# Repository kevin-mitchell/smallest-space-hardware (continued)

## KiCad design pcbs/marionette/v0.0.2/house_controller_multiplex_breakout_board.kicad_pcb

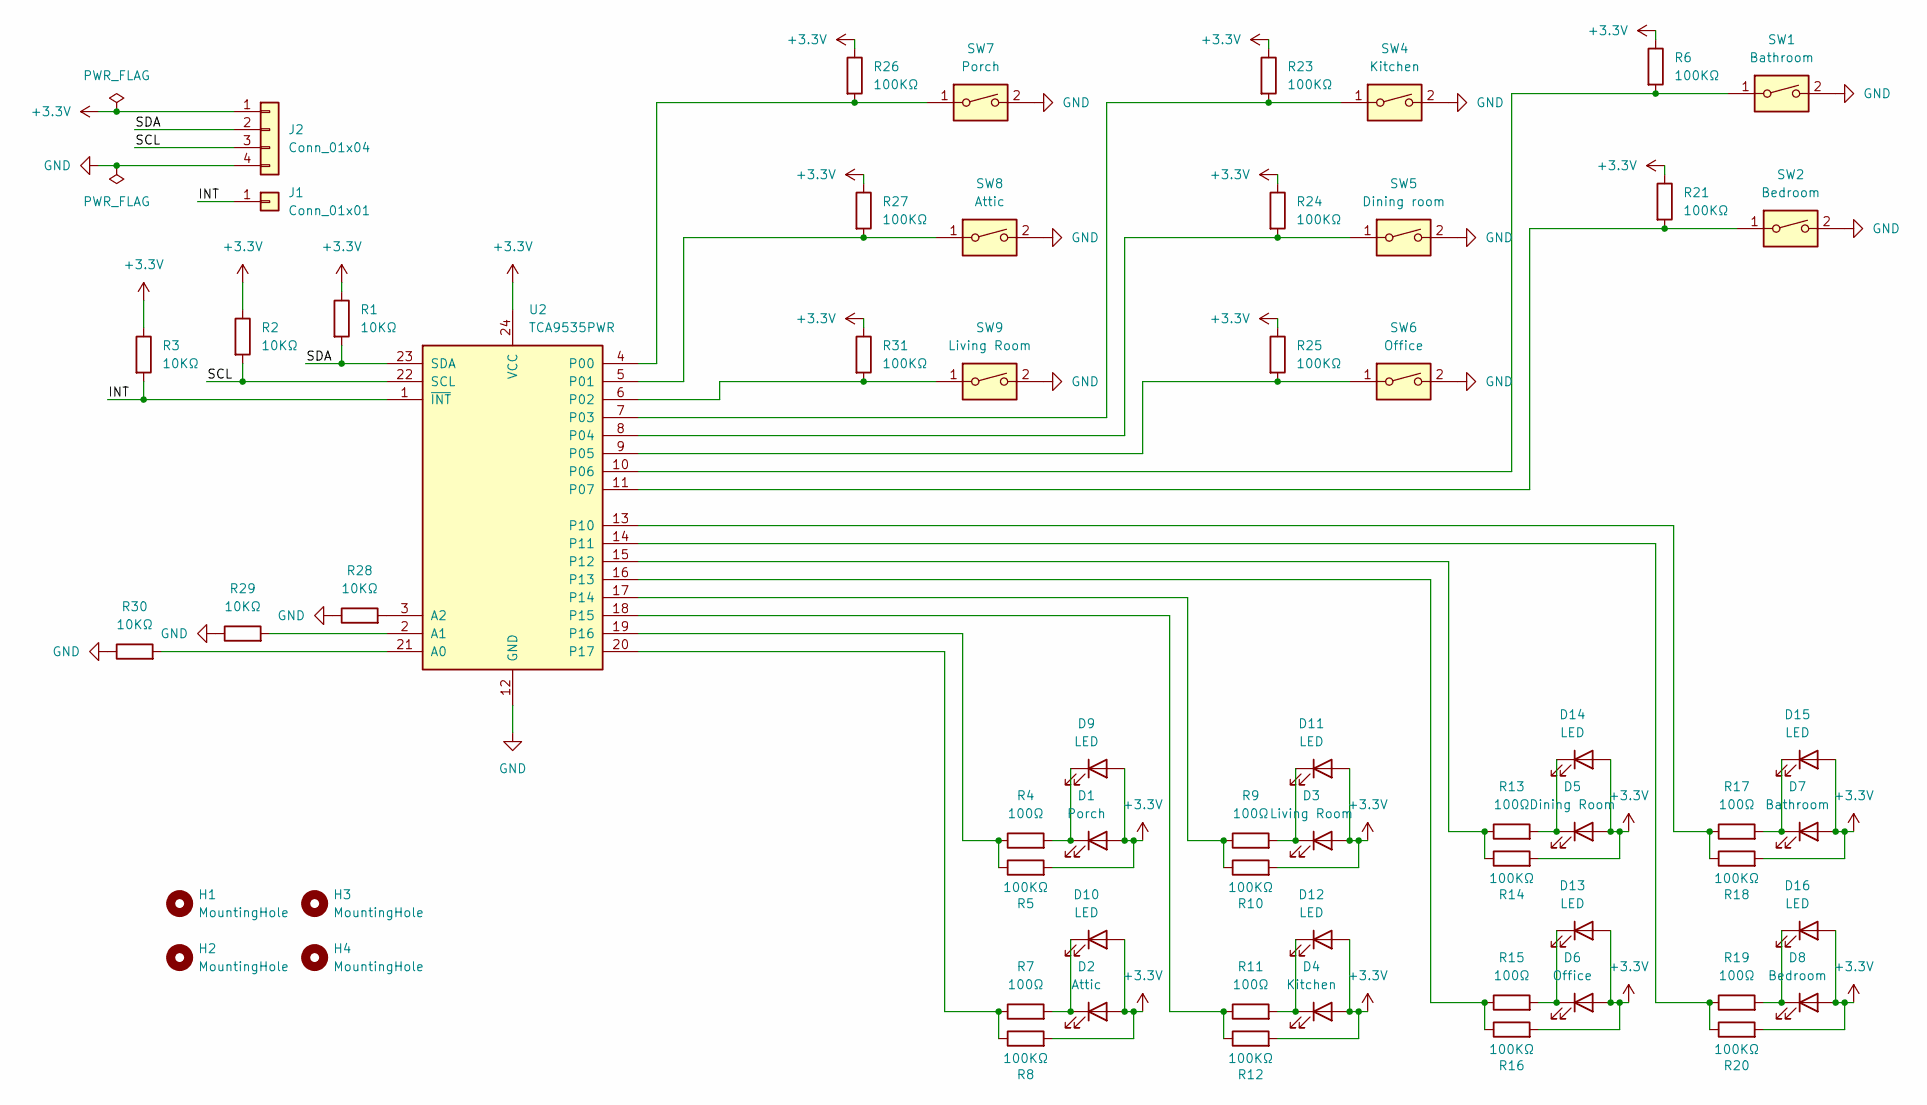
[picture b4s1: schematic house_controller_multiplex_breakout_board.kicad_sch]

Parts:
D1: Porch; LED_0805_2012Metric_Pad1.15x1.40mm_HandSolder
D2: Attic; LED_0805_2012Metric_Pad1.15x1.40mm_HandSolder
D3: Living Room; LED_0805_2012Metric_Pad1.15x1.40mm_HandSolder
D4: Kitchen; LED_0805_2012Metric_Pad1.15x1.40mm_HandSolder
D5: Dining Room; LED_0805_2012Metric_Pad1.15x1.40mm_HandSolder
D6: Office; LED_0805_2012Metric_Pad1.15x1.40mm_HandSolder
D7: Bathroom; LED_0805_2012Metric_Pad1.15x1.40mm_HandSolder
D8: Bedroom; LED_0805_2012Metric_Pad1.15x1.40mm_HandSolder
D9, D10, D11, D12, D13, D14, D15, D16: LED; LED_D3.0mm
H1, H2, H3, H4: MountingHole; MountingHole_2.5mm
J1: Conn_01x01; PinSocket_1x01_P2.54mm_Vertical
J2: Conn_01x04; PinSocket_1x04_P2.54mm_Vertical
R1, R2, R3, R28, R29, R30: 10KΩ; R_0805_2012Metric_Pad1.20x1.40mm_HandSolder
R4, R7, R9, R11, R13, R15, R17, R19: 100Ω; R_0805_2012Metric_Pad1.20x1.40mm_HandSolder
R5, R6, R8, R10, R12, R14, R16, R18, R20, R21, R23, R24, R25, R26, R27, R31: 100KΩ; R_0805_2012Metric_Pad1.20x1.40mm_HandSolder
SW1: Bathroom; SW_DIP_SPSTx01_Slide_9.78x4.72mm_W7.62mm_P2.54mm
SW2: Bedroom; SW_DIP_SPSTx01_Slide_9.78x4.72mm_W7.62mm_P2.54mm
SW4: Kitchen; SW_DIP_SPSTx01_Slide_9.78x4.72mm_W7.62mm_P2.54mm
SW5: Dining room; SW_DIP_SPSTx01_Slide_9.78x4.72mm_W7.62mm_P2.54mm
SW6: Office; SW_DIP_SPSTx01_Slide_9.78x4.72mm_W7.62mm_P2.54mm
SW7: Porch; SW_DIP_SPSTx01_Slide_9.78x4.72mm_W7.62mm_P2.54mm
SW8: Attic; SW_DIP_SPSTx01_Slide_9.78x4.72mm_W7.62mm_P2.54mm
SW9: Living Room; SW_DIP_SPSTx01_Slide_9.78x4.72mm_W7.62mm_P2.54mm
U2: TCA9535PWR; TSSOP-24_4.4x7.8mm_P0.65mm

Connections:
+3.3V: D1.2 (A), D2.2 (A), D3.2 (A), D4.2 (A), D5.2 (A), D6.2 (A), D7.2 (A), D8.2 (A), D9.2 (A), D10.2 (A), D11.2 (A), D12.2 (A), D13.2 (A), D14.2 (A), D15.2 (A), D16.2 (A), J2.1, R1.1, R2.1, R3.1, R5.2, R6.1, R8.2, R10.2, R12.2, R14.2, R16.2, R18.2, R20.2, R21.1, R23.1, R24.1, R25.1, R26.1, R27.1, R31.1, U2.24 (VCC)
/INT: J1.1, R3.2, U2.1 (~INT)
/SCL: J2.3, R2.2, U2.22 (SCL)
/SDA: J2.2, R1.2, U2.23 (SDA)
GND: J2.4, R28.1, R29.1, R30.1, SW1.2, SW2.2, SW4.2, SW5.2, SW6.2, SW7.2, SW8.2, SW9.2, U2.12 (GND)
unnamed: D1.1 (K), D9.1 (K), R4.2
unnamed: D2.1 (K), D10.1 (K), R7.2
unnamed: D3.1 (K), D11.1 (K), R9.2
unnamed: D4.1 (K), D12.1 (K), R11.2
unnamed: D6.1 (K), D13.1 (K), R15.2
unnamed: D5.1 (K), D14.1 (K), R13.2
unnamed: D7.1 (K), D15.1 (K), R17.2
unnamed: D8.1 (K), D16.1 (K), R19.2
unnamed: R30.2, U2.21 (A0)
unnamed: R29.2, U2.2 (A1)
unnamed: R28.2, U2.3 (A2)
unnamed: R26.2, SW7.1, U2.4 (P00)
unnamed: R27.2, SW8.1, U2.5 (P01)
unnamed: R31.2, SW9.1, U2.6 (P02)
unnamed: R23.2, SW4.1, U2.7 (P03)
unnamed: R24.2, SW5.1, U2.8 (P04)
unnamed: R25.2, SW6.1, U2.9 (P05)
unnamed: R6.2, SW1.1, U2.10 (P06)
unnamed: R21.2, SW2.1, U2.11 (P07)
unnamed: R17.1, R18.1, U2.13 (P10)
unnamed: R19.1, R20.1, U2.14 (P11)
unnamed: R13.1, R14.1, U2.15 (P12)
unnamed: R15.1, R16.1, U2.16 (P13)
unnamed: R9.1, R10.1, U2.17 (P14)
unnamed: R11.1, R12.1, U2.18 (P15)
unnamed: R4.1, R5.1, U2.19 (P16)
unnamed: R7.1, R8.1, U2.20 (P17)

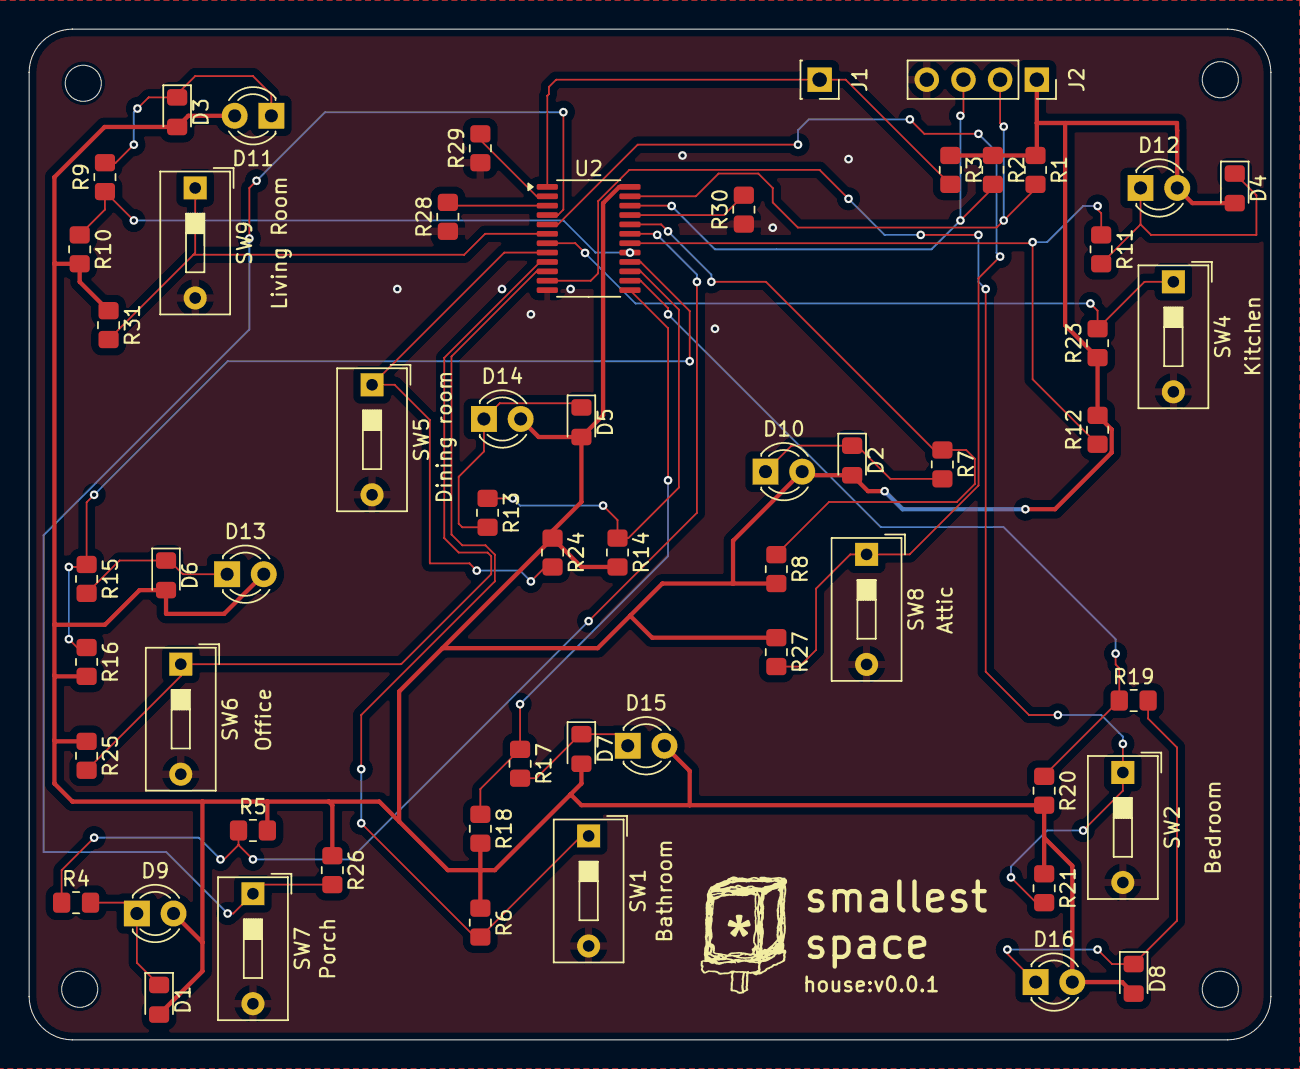
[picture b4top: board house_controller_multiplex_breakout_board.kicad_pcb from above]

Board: 4 copper layers, 86.0 x 70.0 mm, 61 parts (0 on the bottom side), 32 nets.

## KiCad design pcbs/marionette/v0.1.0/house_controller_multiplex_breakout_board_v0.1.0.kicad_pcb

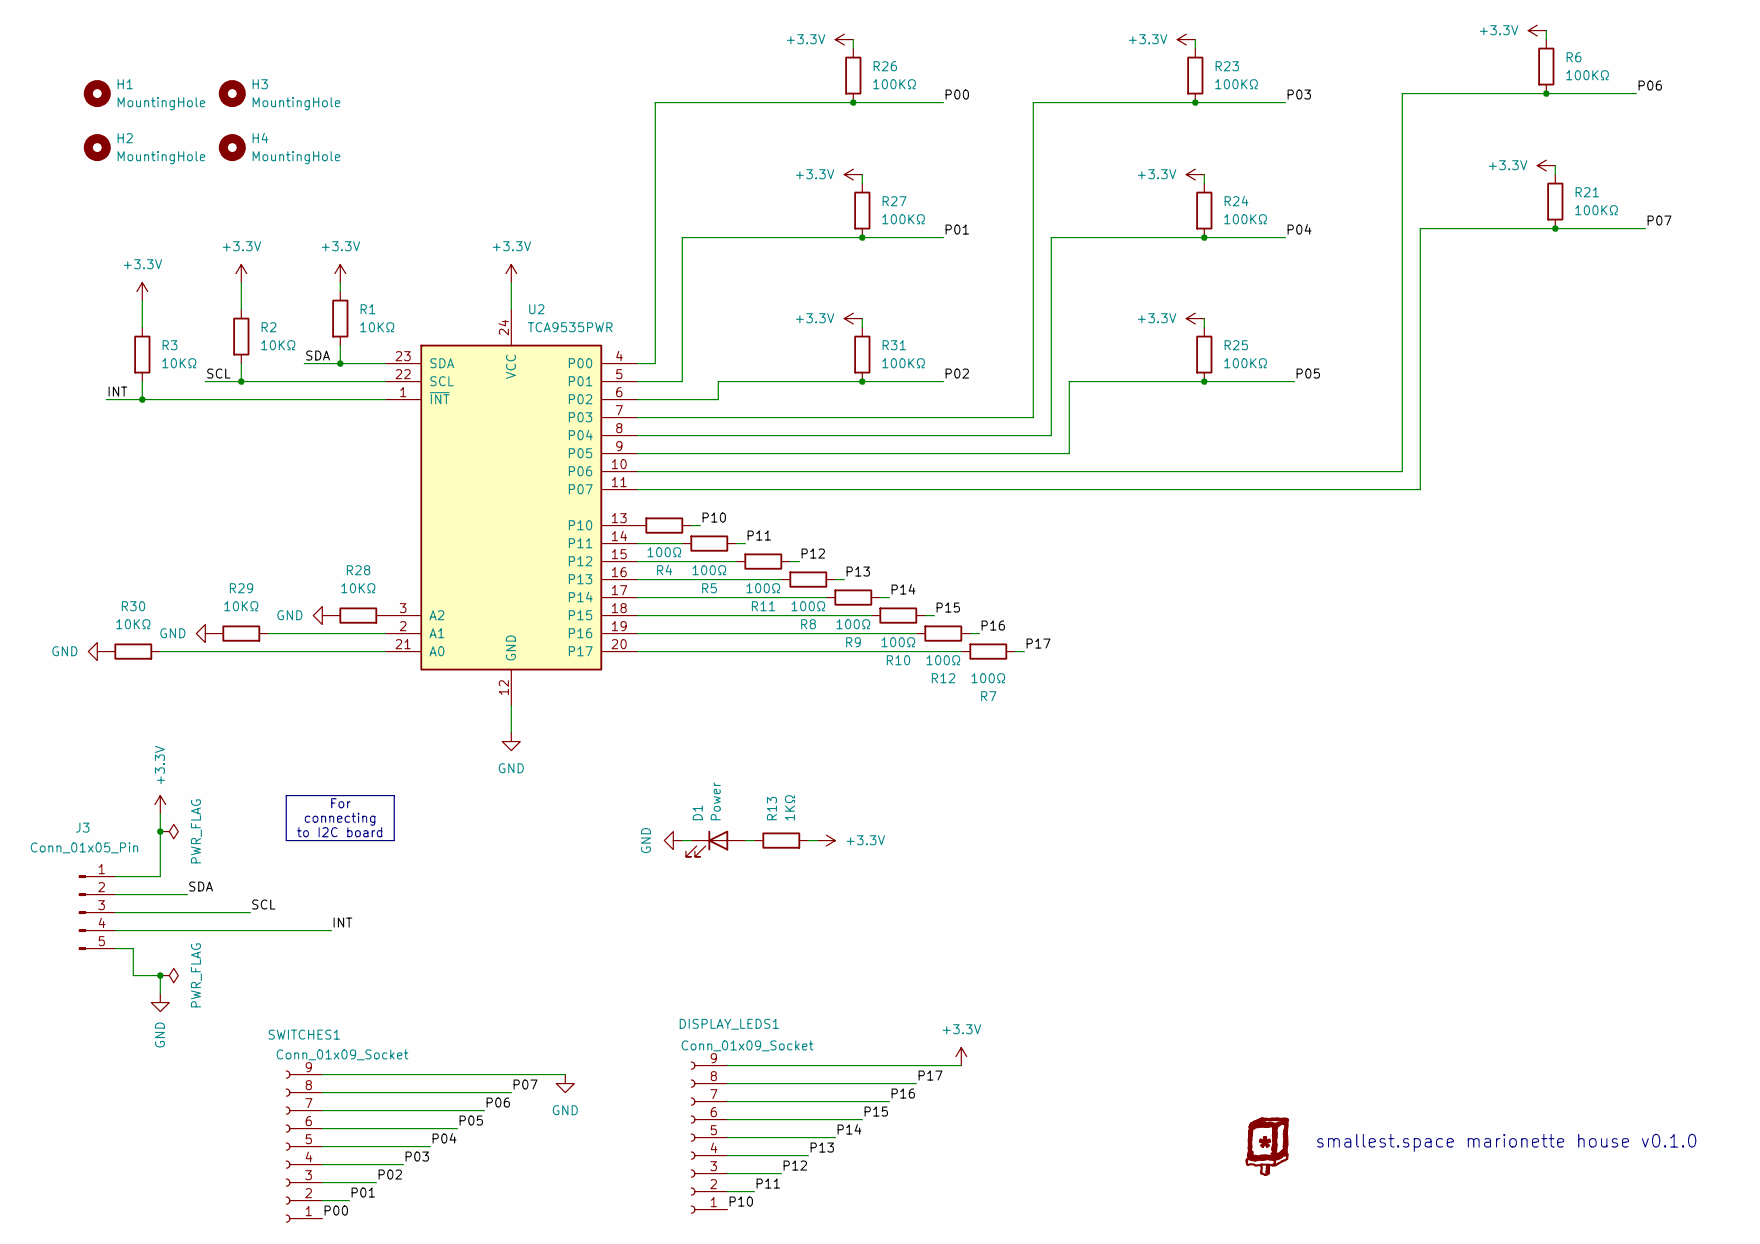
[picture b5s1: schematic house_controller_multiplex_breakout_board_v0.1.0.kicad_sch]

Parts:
D1: Power; LED_0805_2012Metric_Pad1.15x1.40mm_HandSolder
DISPLAY_LEDS1: Conn_01x09_Socket; TBL009-254-09XX-2XX
H1, H2, H3, H4: MountingHole; MountingHole_2.5mm
J3: Conn_01x05_Pin; JST_S05B-PASK-2_1x05_P2.00mm_Side_entry
R1, R2, R3, R28, R29, R30: 10KΩ; R_0805_2012Metric_Pad1.20x1.40mm_HandSolder
R4, R5, R7, R8, R9, R10, R11, R12: 100Ω; R_0805_2012Metric_Pad1.20x1.40mm_HandSolder
R6, R21, R23, R24, R25, R26, R27, R31: 100KΩ; R_0805_2012Metric_Pad1.20x1.40mm_HandSolder
R13: 1KΩ; R_0805_2012Metric_Pad1.20x1.40mm_HandSolder
SWITCHES1: Conn_01x09_Socket; TBL009-254-09XX-2XX
U2: TCA9535PWR; TSSOP-24_4.4x7.8mm_P0.65mm

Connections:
+3.3V: DISPLAY_LEDS1.9, J3.1, R1.1, R2.1, R3.1, R6.1, R13.2, R21.1, R23.1, R24.1, R25.1, R26.1, R27.1, R31.1, U2.24 (VCC)
/INT: J3.4, R3.2, U2.1 (~INT)
/P00: R26.2, SWITCHES1.1, U2.4 (P00)
/P01: R27.2, SWITCHES1.2, U2.5 (P01)
/P02: R31.2, SWITCHES1.3, U2.6 (P02)
/P03: R23.2, SWITCHES1.4, U2.7 (P03)
/P04: R24.2, SWITCHES1.5, U2.8 (P04)
/P05: R25.2, SWITCHES1.6, U2.9 (P05)
/P06: R6.2, SWITCHES1.7, U2.10 (P06)
/P07: R21.2, SWITCHES1.8, U2.11 (P07)
/P10: DISPLAY_LEDS1.1, R4.1
/P11: DISPLAY_LEDS1.2, R5.1
/P12: DISPLAY_LEDS1.3, R11.1
/P13: DISPLAY_LEDS1.4, R8.1
/P14: DISPLAY_LEDS1.5, R9.1
/P15: DISPLAY_LEDS1.6, R10.1
/P16: DISPLAY_LEDS1.7, R12.1
/P17: DISPLAY_LEDS1.8, R7.1
/SCL: J3.3, R2.2, U2.22 (SCL)
/SDA: J3.2, R1.2, U2.23 (SDA)
GND: D1.1 (K), J3.5, R28.1, R29.1, R30.1, SWITCHES1.9, U2.12 (GND)
unnamed: D1.2 (A), R13.1
unnamed: R30.2, U2.21 (A0)
unnamed: R29.2, U2.2 (A1)
unnamed: R28.2, U2.3 (A2)
unnamed: R4.2, U2.13 (P10)
unnamed: R5.2, U2.14 (P11)
unnamed: R11.2, U2.15 (P12)
unnamed: R8.2, U2.16 (P13)
unnamed: R9.2, U2.17 (P14)
unnamed: R10.2, U2.18 (P15)
unnamed: R12.2, U2.19 (P16)
unnamed: R7.2, U2.20 (P17)

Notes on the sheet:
For connecting to I2C board
smallest.space marionette house v0.1.0

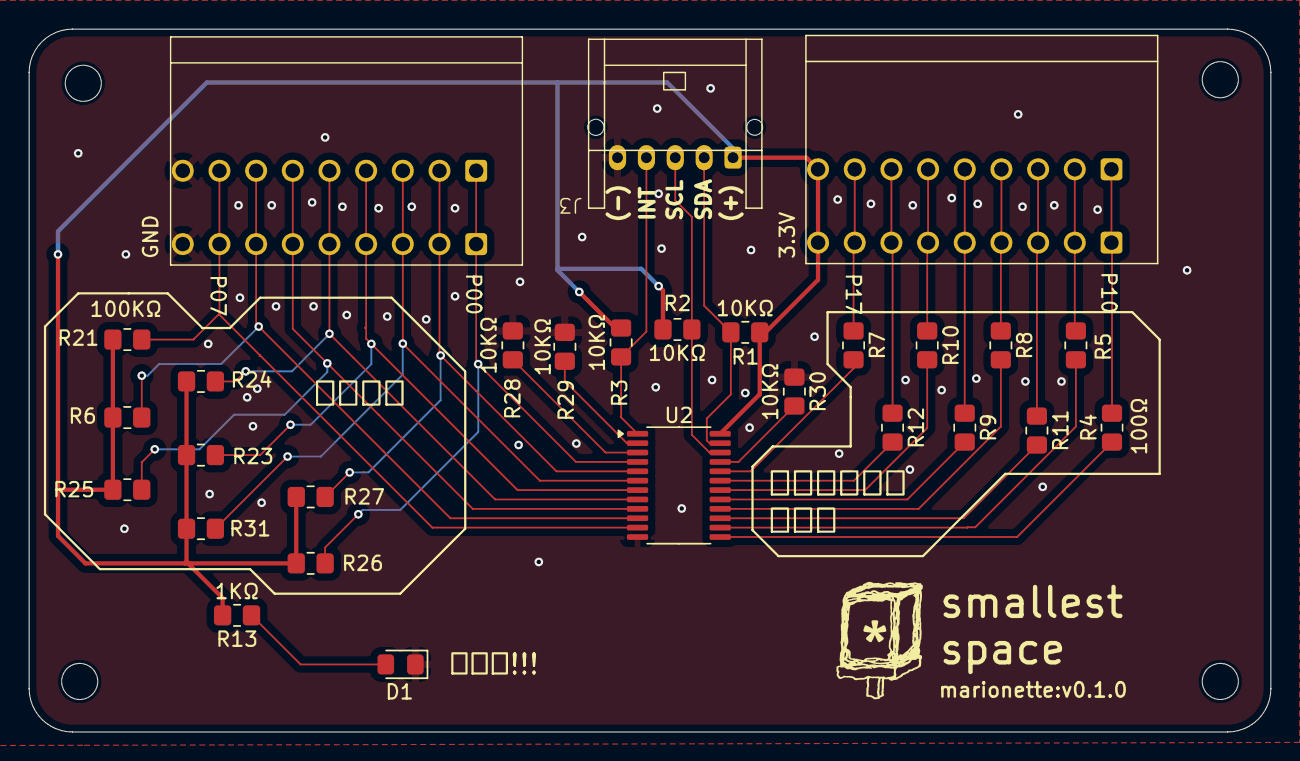
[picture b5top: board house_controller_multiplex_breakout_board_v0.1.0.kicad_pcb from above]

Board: 4 copper layers, 86.0 x 48.7 mm, 32 parts (0 on the bottom side), 33 nets.

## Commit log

2025-01-27 add marionette 0.1.0 and main 0.3.0
2025-03-05 add main v0.3.1 and marionette v0.2.2
2026-04-28 starting the web radio design and including libraries
2026-04-28 adding libraries
2026-04-28 fix libraries and update schematics
2026-04-30 switching to some 0603 passives
2026-05-02 add version 1
2026-05-02 add next version
2026-05-03 Web radio first version (#1)
    * starting the web radio design and including libraries
    * adding libraries
    * fix libraries and update schematics
    * switching to some 0603 passives
    * add version 1
    * add next version
